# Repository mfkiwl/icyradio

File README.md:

# icyradio

A **S**oftware **D**efined **R**adio development board.

Initial project codename **Icy**radio originated from the device family name of the FPGA used in the [first version](https://github.com/vankxr/icyradio/tree/v1/qo100) (**ICE**40). Coincidently, the device family name of the FPGA used in this version (Artix) also resembles a very cold region, the Arctic, hence, the project codename still holds some of its sense :blush:.

## Main components
 - [XC7A100T-2FGG484](https://pt.mouser.com/datasheet/2/903/ds180_7Series_Overview-1591537.pdf) - FPGA
 - [Raspberry Pi CM4](https://datasheets.raspberrypi.com/cm4/cm4-datasheet.pdf) - Raspberry Pi Compute Module 4
 - [MT41K256M16TW-125](https://media-www.micron.com/-/media/client/global/documents/products/data-sheet/dram/ddr3/4gb_1_35v_ddr3l_xit_addendum.pdf?rev=993cd23ec9f2450c8cae38fcb35343bd) - DDR3 RAM
 - [AD9361](https://github.com/vankxr/icyradio/raw/v2/qo100/docs/ad9361_transceiver/AD9361_Datasheet_RevF.pdf) - Agile RF Transceiver
 - [SI5351C](https://www.silabs.com/documents/public/data-sheets/Si5351-B.pdf) - System clock synthesizer
 - [8V97003](https://www.renesas.com/us/en/document/dst/8v97003-datasheet?r=462341) - Frequency Synthesizer for external mixer support
 - [ADAU1372](https://www.analog.com/media/en/technical-documentation/data-sheets/ADAU1372.pdf) - Audio CODEC
 - [UPD301C](https://ww1.microchip.com/downloads/aemDocuments/documents/UNG/ProductDocuments/DataSheets/00003412A.pdf) - USB Power Delivery controller
 - [LT7182S](https://www.analog.com/media/en/technical-documentation/data-sheets/lt7182s.pdf) - Main Buck regulator

## Functional block diagram

#### v2
**Note: From v2 onwards, the only components in this repository are hardware related, no specific application software, like in v1 branches. Applications that use this hardware are kept in a separate [repository](https://github.com/vankxr/icyradio-apps)**
The goal of this project is to develop a flexible and feature rich SDR platform for tinkering. It will include, among other features, a mmWave synthesizer controlled by software to allow external mixers to be attached to the SDR and extend its frequency range (i.e. for 5G applications), and also allow interfacing to a Raspberry Pi Compute Module 4 for standalone operation.

## Dependencies
 - [vivado](https://www.xilinx.com/support/download.html) - FPGA toolchain
 - [arm-none-eabi-gcc](https://developer.arm.com/tools-and-software/open-source-software/developer-tools/gnu-toolchain/gnu-rm/downloads) - PD Controller MCU toolchain
 - [Device CMSIS](https://www.keil.com/dd2/) - CMSIS headers defining the MCU memories, peripherals, etc...
 - [Core CMSIS](https://github.com/ARM-software/CMSIS_5) - CMSIS headers defining the ARM Cores
 - [armmem](https://github.com/vankxr/armmem) - ELF file analyzer (required for the MCU Makefiles to work)
 - [SoapySDR](https://github.com/pothosware/SoapySDR) - Vendor and platform neutral SDR support library

## Software build instructions
TODO (In the meantime, check the github workflows)
### Kernel driver
TODO
### SoapySDR device driver
TODO

## Errata
 - The WP pin of the LT7182S regulator was left floating, with a placeholder resistor for pulling it up later, assuming it had an internal pulldown. Turns out it is floating, and thus it can be sampled internally as 1, write-protecting the device and forbidding configuration commands. A quick fix is to scrape a tiny bit of the ground plane near the WP resistor (R1120) pad, and shunting it to GND there with a blob of solder. The figure below exemplifies the process. The solder blob is marked in blue.

 - The FPGA INIT and DONE LED markings on the PCB are swapped (oops). In the picture below, it can be seen that D202 connects to the FPGA_DONE signal, yet it's labelled INIT. The FPGA_INIT signal connects to D201, and is labelled as DONE. It is merely an aesthetic problem, and does not affect functionality at all!

## Authors

* **João Silva** - [vankxr](https://github.com/vankxr)

## License

The content of this repository is licensed under the [GNU General Public License v3.0](LICENSE).

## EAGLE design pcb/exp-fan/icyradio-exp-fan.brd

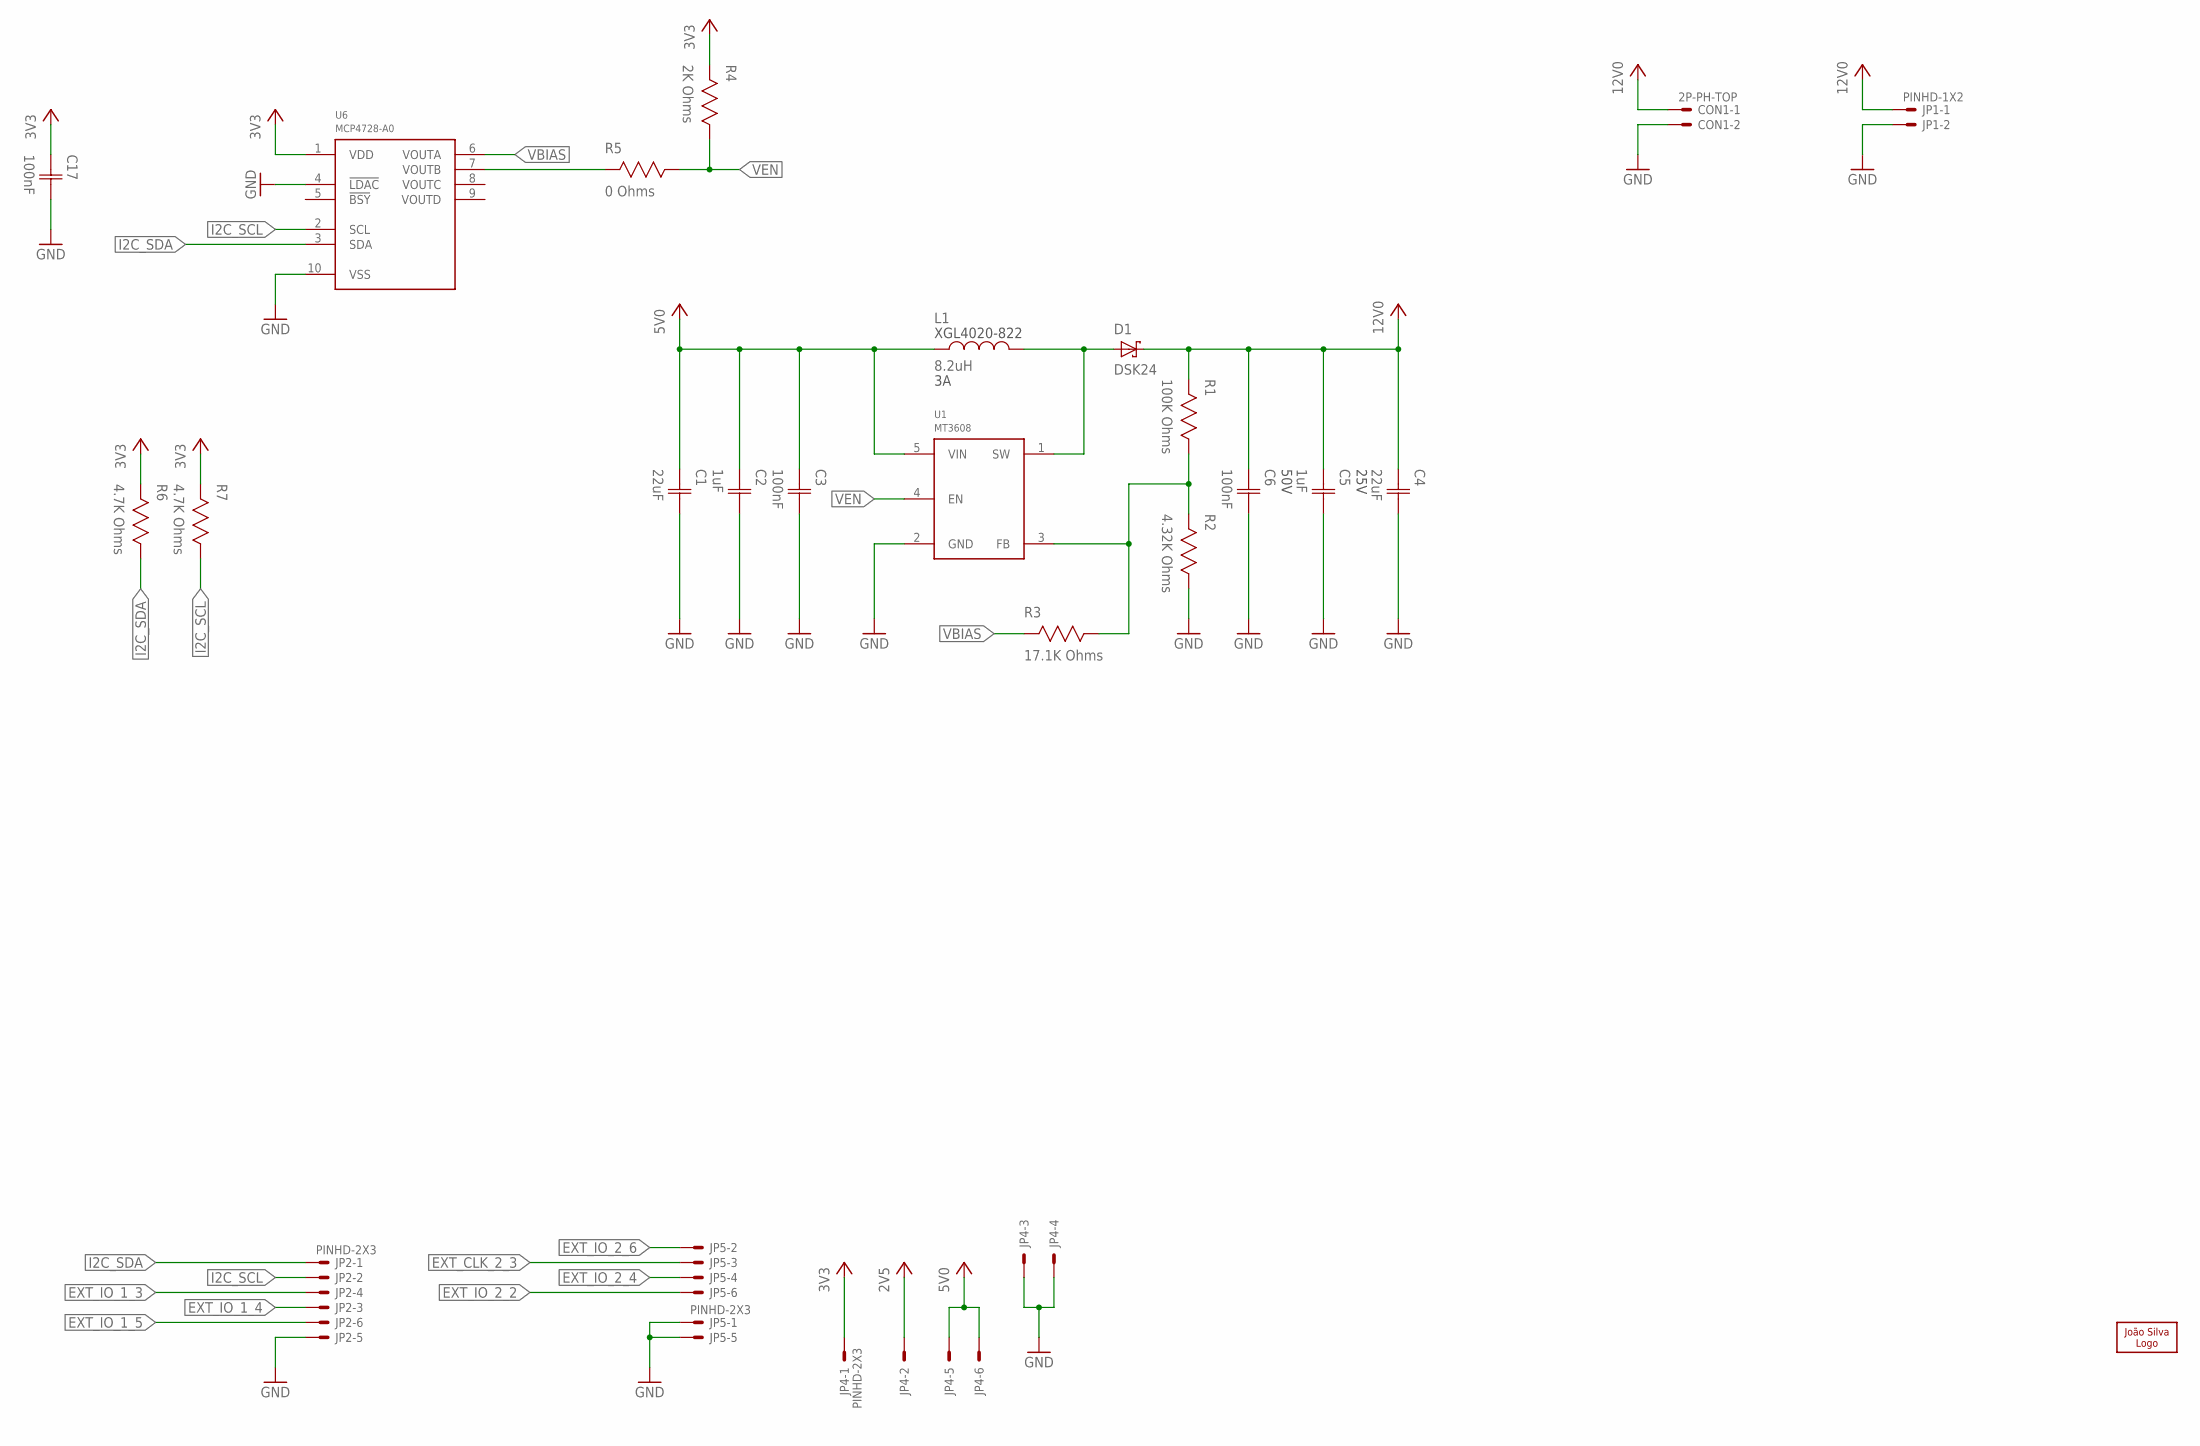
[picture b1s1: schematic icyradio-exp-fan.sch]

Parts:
C1: 22uF; CAP1206
C2: 1uF; CAP0402
C3, C6, C17: 100nF; CAP0402
C4: 22uF; CAP1206; VOLTAGE 25V
C5: 1uF; CAP0402; VOLTAGE 50V
CON1: 2P-PH-TOP; PH-02-TOP
D1: DSK24; SOD-123F
JP1: PINHD-1X2; 1X02
JP2, JP4, JP5: PINHD-2X3; 2X03
L1: 8.2uH; XGL4020
LOGO1: JSILVA-10MM; JSILVA_10MM
R1: 100K Ohms; RES0402
R2: 4.32K Ohms; RES0402
R3: 17.1K Ohms; RES0402
R4: 2K Ohms; RES0402
R5: 0 Ohms; RES0402
R6, R7: 4.7K Ohms; RES0402
U1: MT3608; SOT23-6
U6: MCP4728-A0; MSOP10

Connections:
2V5: JP4.2
3V3: C17.1 (C1), JP4.1, R4.2, R6.2, R7.2, U6.1 (VDD)
5V0: C1.1 (C1), C2.1 (C1), C3.1 (C1), JP4.5, JP4.6, L1.1, U1.5 (VIN)
12V0: C4.1 (C1), C5.1 (C1), C6.1 (C1), CON1.1, D1.C, JP1.1, R1.2
EXT_CLK_2_3: JP5.3
EXT_IO_1_3: JP2.4
EXT_IO_1_4: JP2.3
EXT_IO_1_5: JP2.6
EXT_IO_2_2: JP5.6
EXT_IO_2_4: JP5.4
EXT_IO_2_6: JP5.2
FB: R1.1, R2.2, R3.1, U1.3 (FB)
GND: C1.2 (C2), C2.2 (C2), C3.2 (C2), C4.2 (C2), C5.2 (C2), C6.2 (C2), C17.2 (C2), CON1.2, JP1.2, JP2.5, JP4.3, JP4.4, JP5.1, JP5.5, R2.1, U1.2 (GND), U6.4 (!LDAC), U6.10 (VSS)
I2C_SCL: JP2.2, R7.1, U6.2 (SCL)
I2C_SDA: JP2.1, R6.1, U6.3 (SDA)
SW: D1.A, L1.2, U1.1 (SW)
VBIAS: R3.2, U6.6 (VOUTA)
VDAC_EN: R5.2, U6.7 (VOUTB)
VEN: R4.1, R5.1, U1.4 (EN)

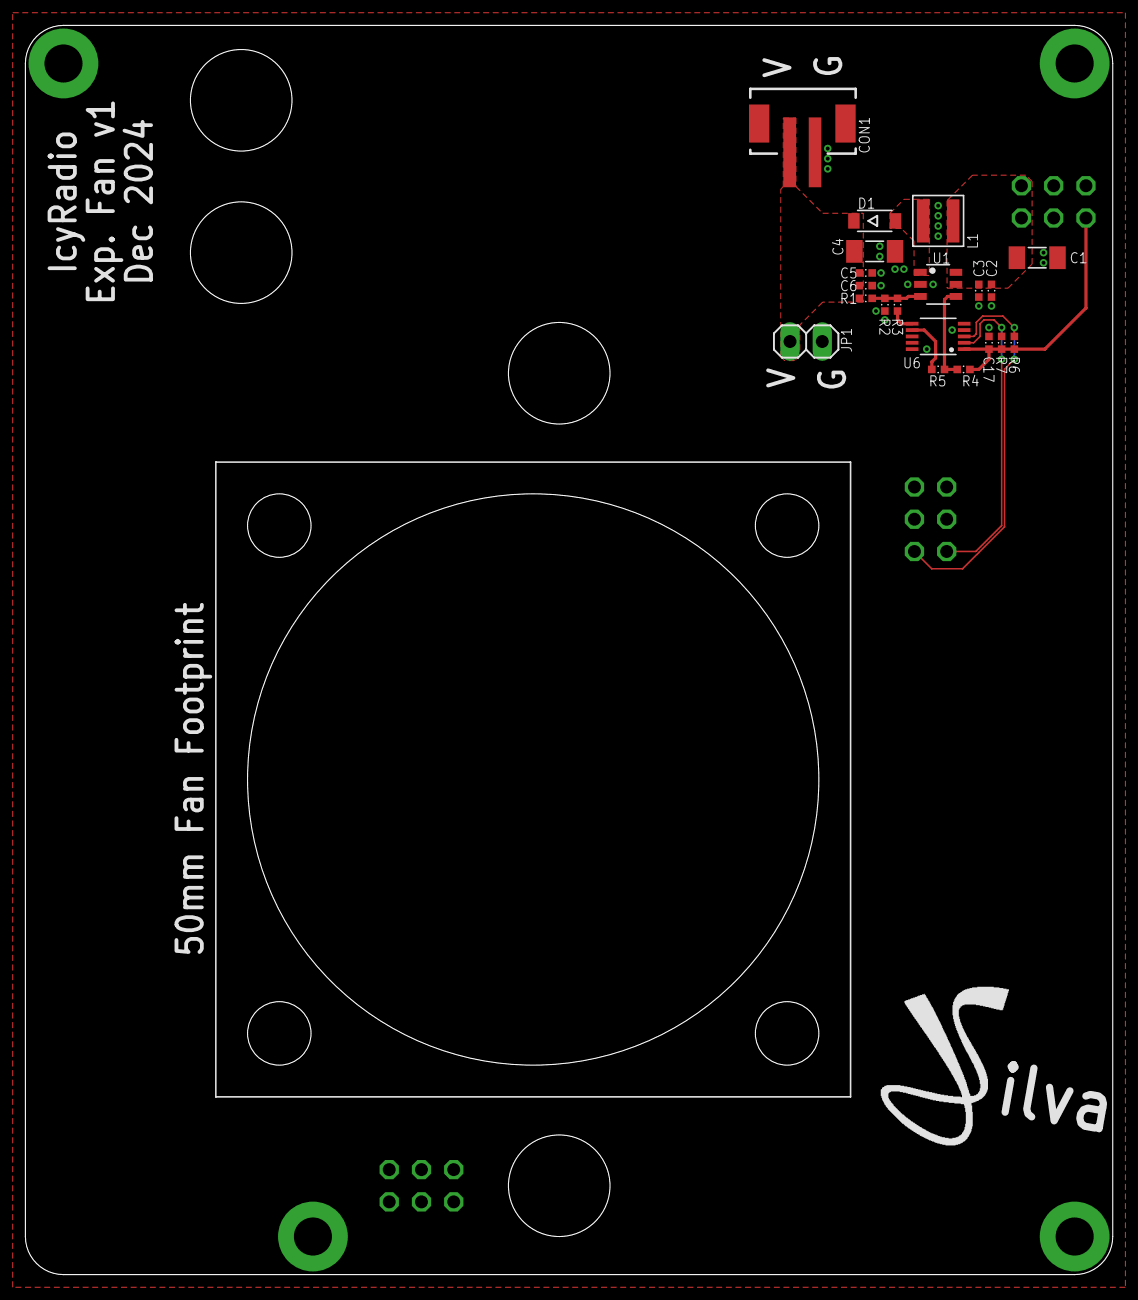
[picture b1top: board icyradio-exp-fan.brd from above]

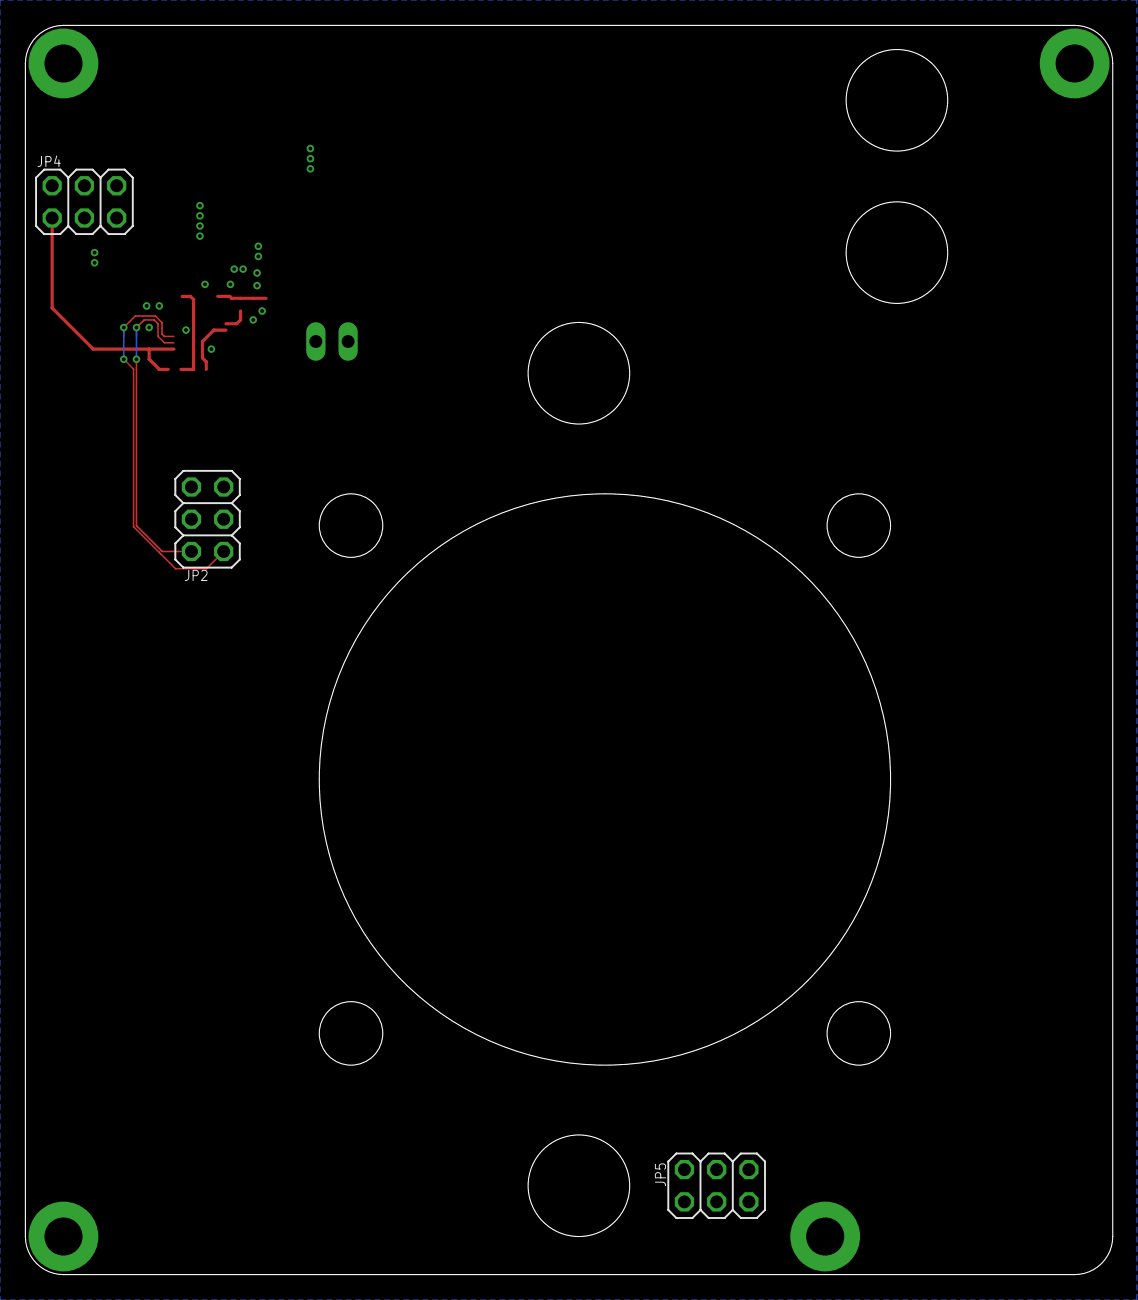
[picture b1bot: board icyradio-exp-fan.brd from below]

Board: 2 copper layers, 85.7 x 98.4 mm, 24 parts (3 on the bottom side), 11 nets.

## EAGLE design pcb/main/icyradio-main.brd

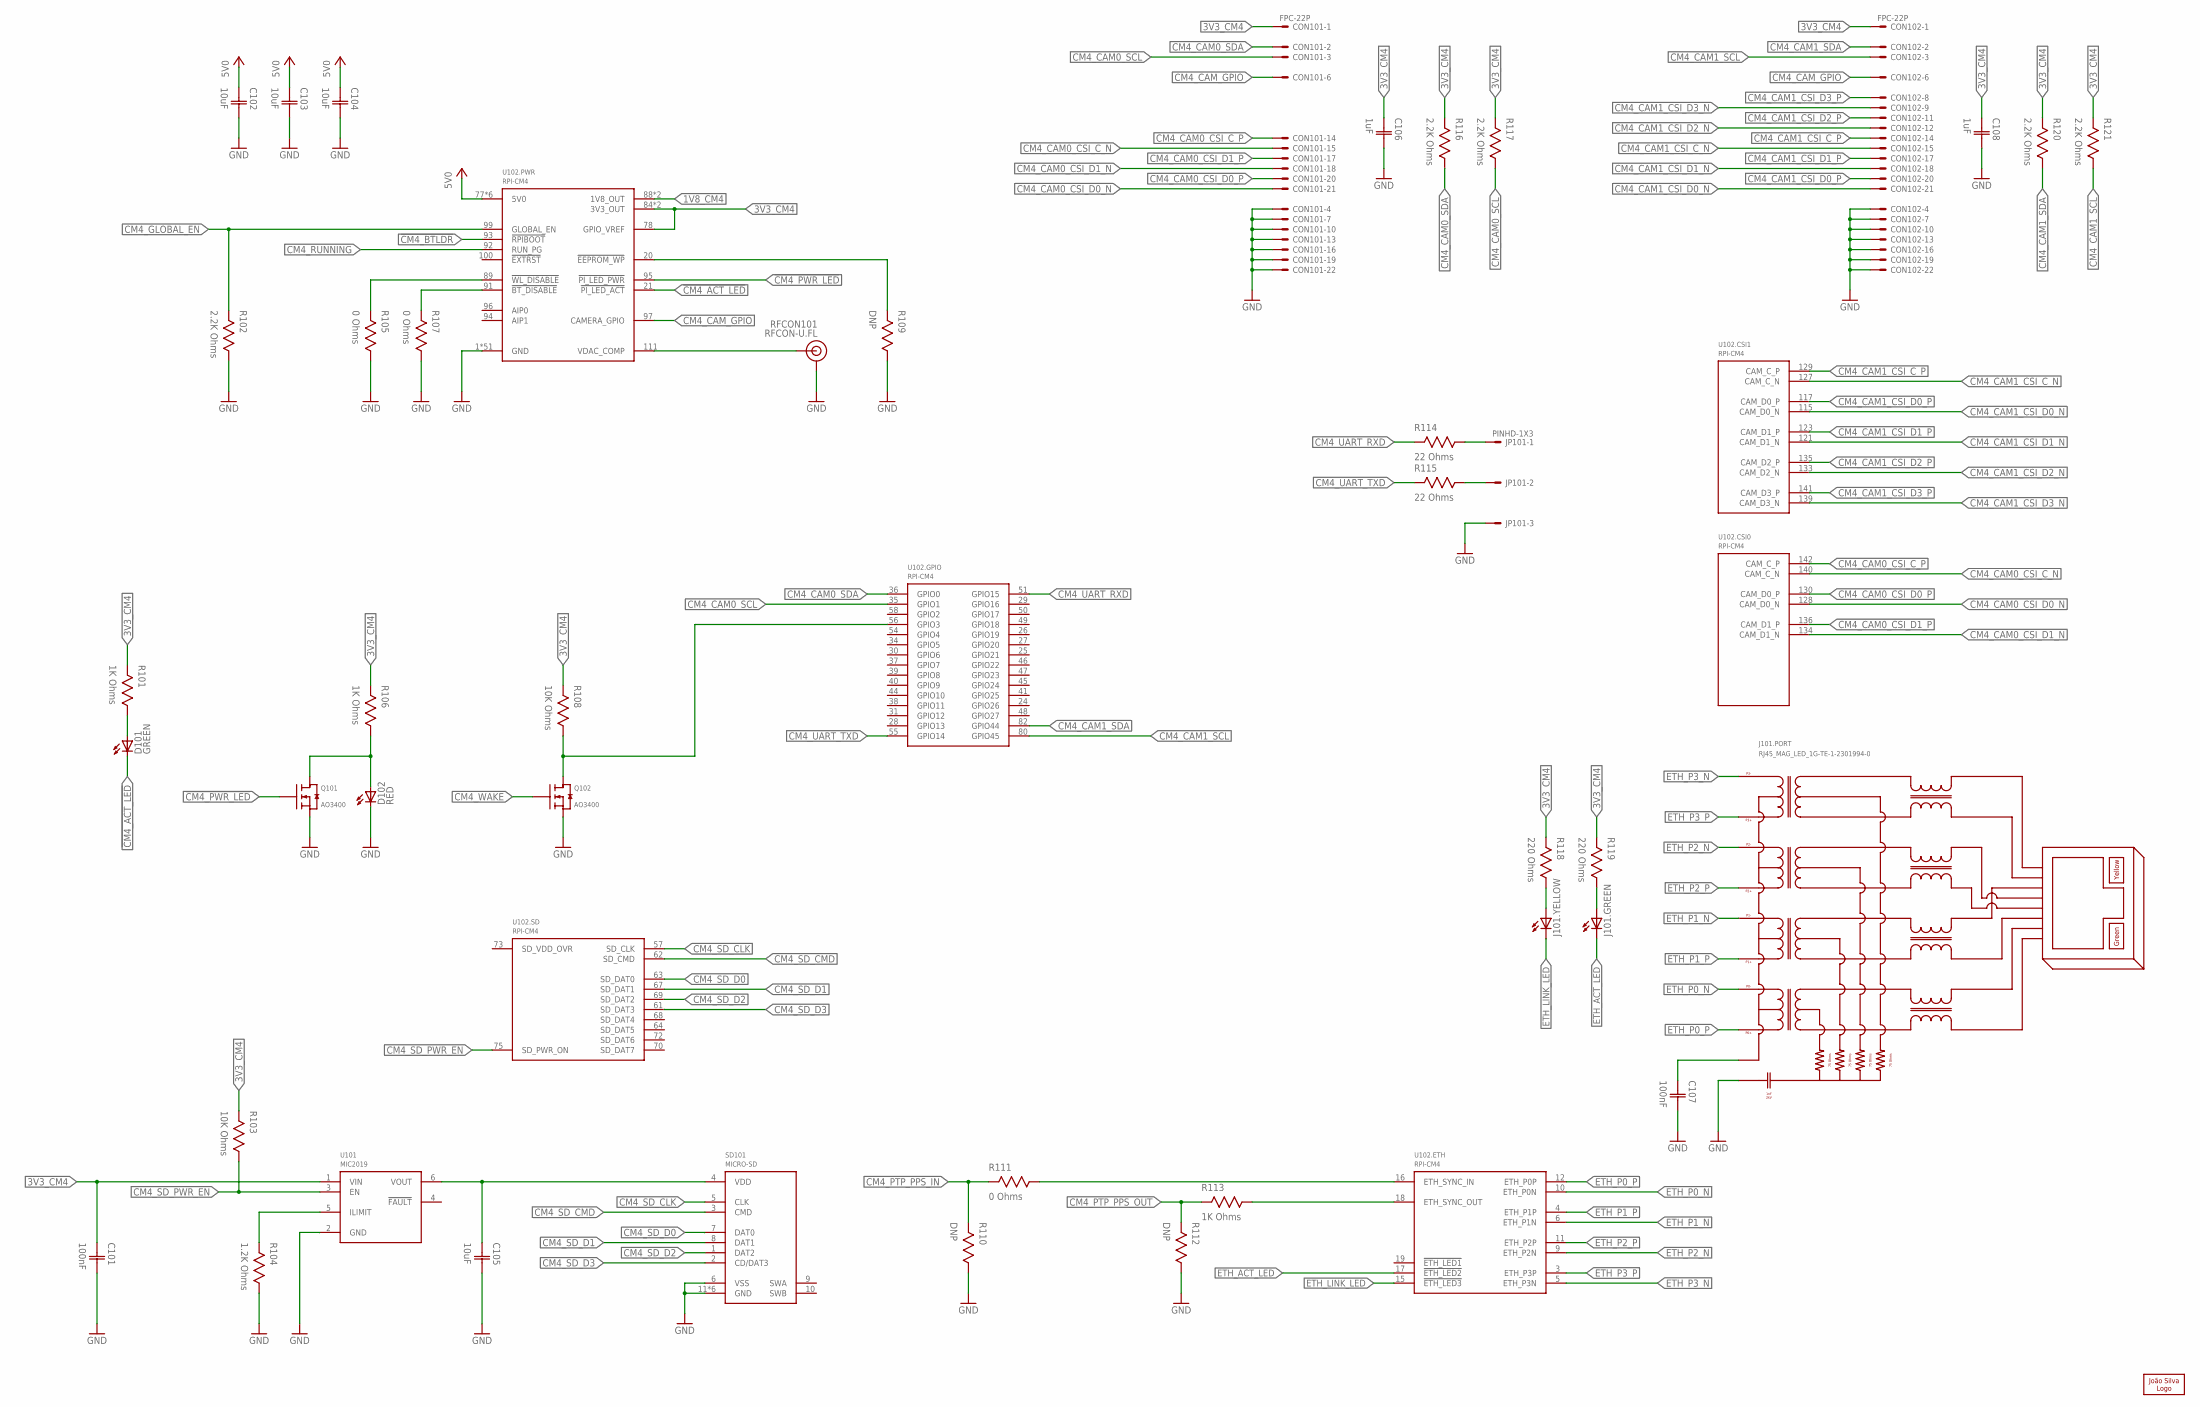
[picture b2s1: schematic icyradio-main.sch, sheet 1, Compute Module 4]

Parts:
C101, C107: 100nF; CAP0402
C102, C103, C104: 10uF; CAP0603
C105: 10uF; CAP0402
C106, C108: 1uF; CAP0402
CON101, CON102: FPC-22P
D101, D102: LED0603; 0603
J101: RJ45_MAG_LED_1G-TE-1-2301994-0; TE-1-2301994-0
JP101: PINHD-1X3; 1X03
LOGO101: JS-10MM; JS_10MM
Q101, Q102: AO3400; SOT23
R101, R106, R113: 1K Ohms; RES0402
R102, R116, R117, R120, R121: 2.2K Ohms; RES0402
R103, R108: 10K Ohms; RES0402
R104: 1.2K Ohms; RES0402
R105, R107, R111: 0 Ohms; RES0402
R109, R110, R112: DNP; RES0402
R114, R115: 22 Ohms; RES0402
R118, R119: 220 Ohms; RES0402
RFCON101: RFCON-U.FL; U.FL
SD101: MICRO-SD; TE-2201778-1
U101: MIC2019; SOT23-6
U102: RPI-CM4

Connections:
1V8_CM4: U102.88 (1V8_OUT), U102.90 (1V8_OUT)
3V3_CM4: C101.1 (C1), C106.1 (C1), C108.1 (C1), CON101.1, CON102.1, R101.2, R103.2, R106.2, R108.2, R116.2, R117.2, R118.2, R119.2, R120.2, R121.2, U101.1 (VIN), U102.78 (GPIO_VREF), U102.84 (3V3_OUT), U102.86 (3V3_OUT); also elsewhere on the board
3V3_CM4_SD: C105.1 (C1), SD101.4 (VDD), U101.6 (VOUT)
5V0: C102.1 (C1), C103.1 (C1), C104.1 (C1), U102.77 (5V0), U102.79 (5V0), U102.81 (5V0), U102.83 (5V0), U102.85 (5V0), U102.87 (5V0); also elsewhere on the board
!CM4_ACT_LED: D101.C, U102.21 (!PI_LED_ACT)
!CM4_BTLDR: U102.93 (!RPIBOOT); also elsewhere on the board
!CM4_BT_DIS: R107.2, U102.91 (!BT_DISABLE)
!CM4_EE_WP: R109.2, U102.20 (!EEPROM_WP)
!CM4_PWR_LED: Q101.1 (G), U102.95 (!PI_LED_PWR)
!CM4_WL_DIS: R105.2, U102.89 (!WL_DISABLE)
CM4_CAM0_CSI_C_N: CON101.15, U102.140 (CAM_C_N)
CM4_CAM0_CSI_C_P: CON101.14, U102.142 (CAM_C_P)
CM4_CAM0_CSI_D0_N: CON101.21, U102.128 (CAM_D0_N)
CM4_CAM0_CSI_D0_P: CON101.20, U102.130 (CAM_D0_P)
CM4_CAM0_CSI_D1_N: CON101.18, U102.134 (CAM_D1_N)
CM4_CAM0_CSI_D1_P: CON101.17, U102.136 (CAM_D1_P)
CM4_CAM0_SCL: CON101.3, R117.1, U102.35 (GPIO1)
CM4_CAM0_SDA: CON101.2, R116.1, U102.36 (GPIO0)
CM4_CAM1_CSI_C_N: CON102.15, U102.127 (CAM_C_N)
CM4_CAM1_CSI_C_P: CON102.14, U102.129 (CAM_C_P)
CM4_CAM1_CSI_D0_N: CON102.21, U102.115 (CAM_D0_N)
CM4_CAM1_CSI_D0_P: CON102.20, U102.117 (CAM_D0_P)
CM4_CAM1_CSI_D1_N: CON102.18, U102.121 (CAM_D1_N)
CM4_CAM1_CSI_D1_P: CON102.17, U102.123 (CAM_D1_P)
CM4_CAM1_CSI_D2_N: CON102.12, U102.133 (CAM_D2_N)
CM4_CAM1_CSI_D2_P: CON102.11, U102.135 (CAM_D2_P)
CM4_CAM1_CSI_D3_N: CON102.9, U102.139 (CAM_D3_N)
CM4_CAM1_CSI_D3_P: CON102.8, U102.141 (CAM_D3_P)
CM4_CAM1_SCL: CON102.3, R121.1, U102.80 (GPIO45)
CM4_CAM1_SDA: CON102.2, R120.1, U102.82 (GPIO44)
CM4_CAM_GPIO: CON101.6, CON102.6, U102.97 (CAMERA_GPIO)
CM4_CVBS: RFCON101.P$3 (SIGNAL), U102.111 (VDAC_COMP)
CM4_GLOBAL_EN: R102.2, U102.99 (GLOBAL_EN); also elsewhere on the board
CM4_GPIO3: Q102.3 (D), R108.1, U102.56 (GPIO3)
CM4_PTP_PPS_IN: R110.2, R111.2; also elsewhere on the board
CM4_PTP_PPS_OUT: R112.2, R113.2; also elsewhere on the board
CM4_RUNNING: U102.92 (RUN_PG); also elsewhere on the board
CM4_SD_CLK: SD101.5 (CLK), U102.57 (SD_CLK)
CM4_SD_CMD: SD101.3 (CMD), U102.62 (SD_CMD)
CM4_SD_D0: SD101.7 (DAT0), U102.63 (SD_DAT0)
CM4_SD_D1: SD101.8 (DAT1), U102.67 (SD_DAT1)
CM4_SD_D2: SD101.1 (DAT2), U102.69 (SD_DAT2)
CM4_SD_D3: SD101.2 (CD/DAT3), U102.61 (SD_DAT3)
CM4_SD_PWR_EN: R103.1, U101.3 (EN), U102.75 (SD_PWR_ON)
CM4_UART_RXD: R114.2, U102.51 (GPIO15)
CM4_UART_TXD: R115.2, U102.55 (GPIO14)
CM4_WAKE: Q102.1 (G); also elsewhere on the board
ETH_ACT_LED: J101.12 (C), U102.17 (!ETH_LED2)
ETH_LINK_LED: J101.14 (C), U102.15 (!ETH_LED3)
ETH_P0_N: J101.3 (P0-), U102.10 (ETH_P0N)
ETH_P0_P: J101.2 (P0+), U102.12 (ETH_P0P)
ETH_P1_N: J101.7 (P1-), U102.6 (ETH_P1N)
ETH_P1_P: J101.4 (P1+), U102.4 (ETH_P1P)
ETH_P2_N: J101.6 (P2-), U102.9 (ETH_P2N)
ETH_P2_P: J101.5 (P2+), U102.11 (ETH_P2P)
ETH_P3_N: J101.9 (P3-), U102.5 (ETH_P3N)
ETH_P3_P: J101.8 (P3+), U102.3 (ETH_P3P)
ETH_SYNC_IN: R111.1, U102.16 (ETH_SYNC_IN)
ETH_SYNC_OUT: R113.1, U102.18 (ETH_SYNC_OUT)
GND: C101.2 (C2), C102.2 (C2), C103.2 (C2), C104.2 (C2), C105.2 (C2), C106.2 (C2), C107.2 (C2), C108.2 (C2), CON101.4, CON101.7, CON101.10, CON101.13, CON101.16, CON101.19, CON101.22, CON102.4, CON102.7, CON102.10, CON102.13, CON102.16, CON102.19, CON102.22, D102.C, J101.10 (CHS_GND), J101.SHIELD@0 (CHS_GND), J101.SHIELD@1 (CHS_GND), JP101.3, Q101.2 (S), Q102.2 (S), R102.1, R104.1, R105.1, R107.1, R109.1, R110.1, R112.1, RFCON101.P$1 (GND), RFCON101.P$2 (GND), SD101.6 (VSS), SD101.11 (GND), SD101.12 (GND), SD101.13 (GND), SD101.14 (GND), SD101.15 (GND), SD101.16 (GND), U101.2 (GND), U102.1 (GND), U102.2 (GND), U102.7 (GND), U102.8 (GND), U102.13 (GND), U102.14 (GND), U102.22 (GND), U102.23 (GND), U102.32 (GND), U102.33 (GND), U102.42 (GND), U102.43 (GND), U102.52 (GND), U102.53 (GND), U102.59 (GND), U102.60 (GND), U102.65 (GND), U102.66 (GND), U102.71 (GND), U102.74 (GND), U102.98 (GND), U102.107 (GND), U102.108 (GND), U102.113 (GND), U102.114 (GND), U102.119 (GND), U102.120 (GND), U102.125 (GND), U102.126 (GND), U102.131 (GND), U102.132 (GND), U102.137 (GND), U102.138 (GND), U102.144 (GND), U102.150 (GND), U102.155 (GND), U102.156 (GND), U102.161 (GND), U102.162 (GND), U102.167 (GND), U102.168 (GND), U102.173 (GND), U102.174 (GND), U102.179 (GND), U102.180 (GND), U102.185 (GND), U102.186 (GND), U102.191 (GND), U102.192 (GND), U102.197 (GND), U102.198 (GND); also elsewhere on the board
unnamed: JP101.1, R114.1
unnamed: JP101.2, R115.1
unnamed: C107.1 (C1), J101.1 (CT)
unnamed: J101.11 (A), R119.1
unnamed: J101.13 (A), R118.1
unnamed: R104.2, U101.5 (ILIMIT)
unnamed: D101.A, R101.1
unnamed: D102.A, Q101.3 (D), R106.1
